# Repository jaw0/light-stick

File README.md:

LED based, battery powered light for photography + videography
modeled after Wescott's "Ice Light"

* aprox 4300 lumens

* 38 Watts

* adjustable power level

* adjustable color temperature: 2700K - 6500K

* consistent + stable output + color even as batteries die

* flicker free

* remembers settings when turned off

* OLED display + touch panel user interface

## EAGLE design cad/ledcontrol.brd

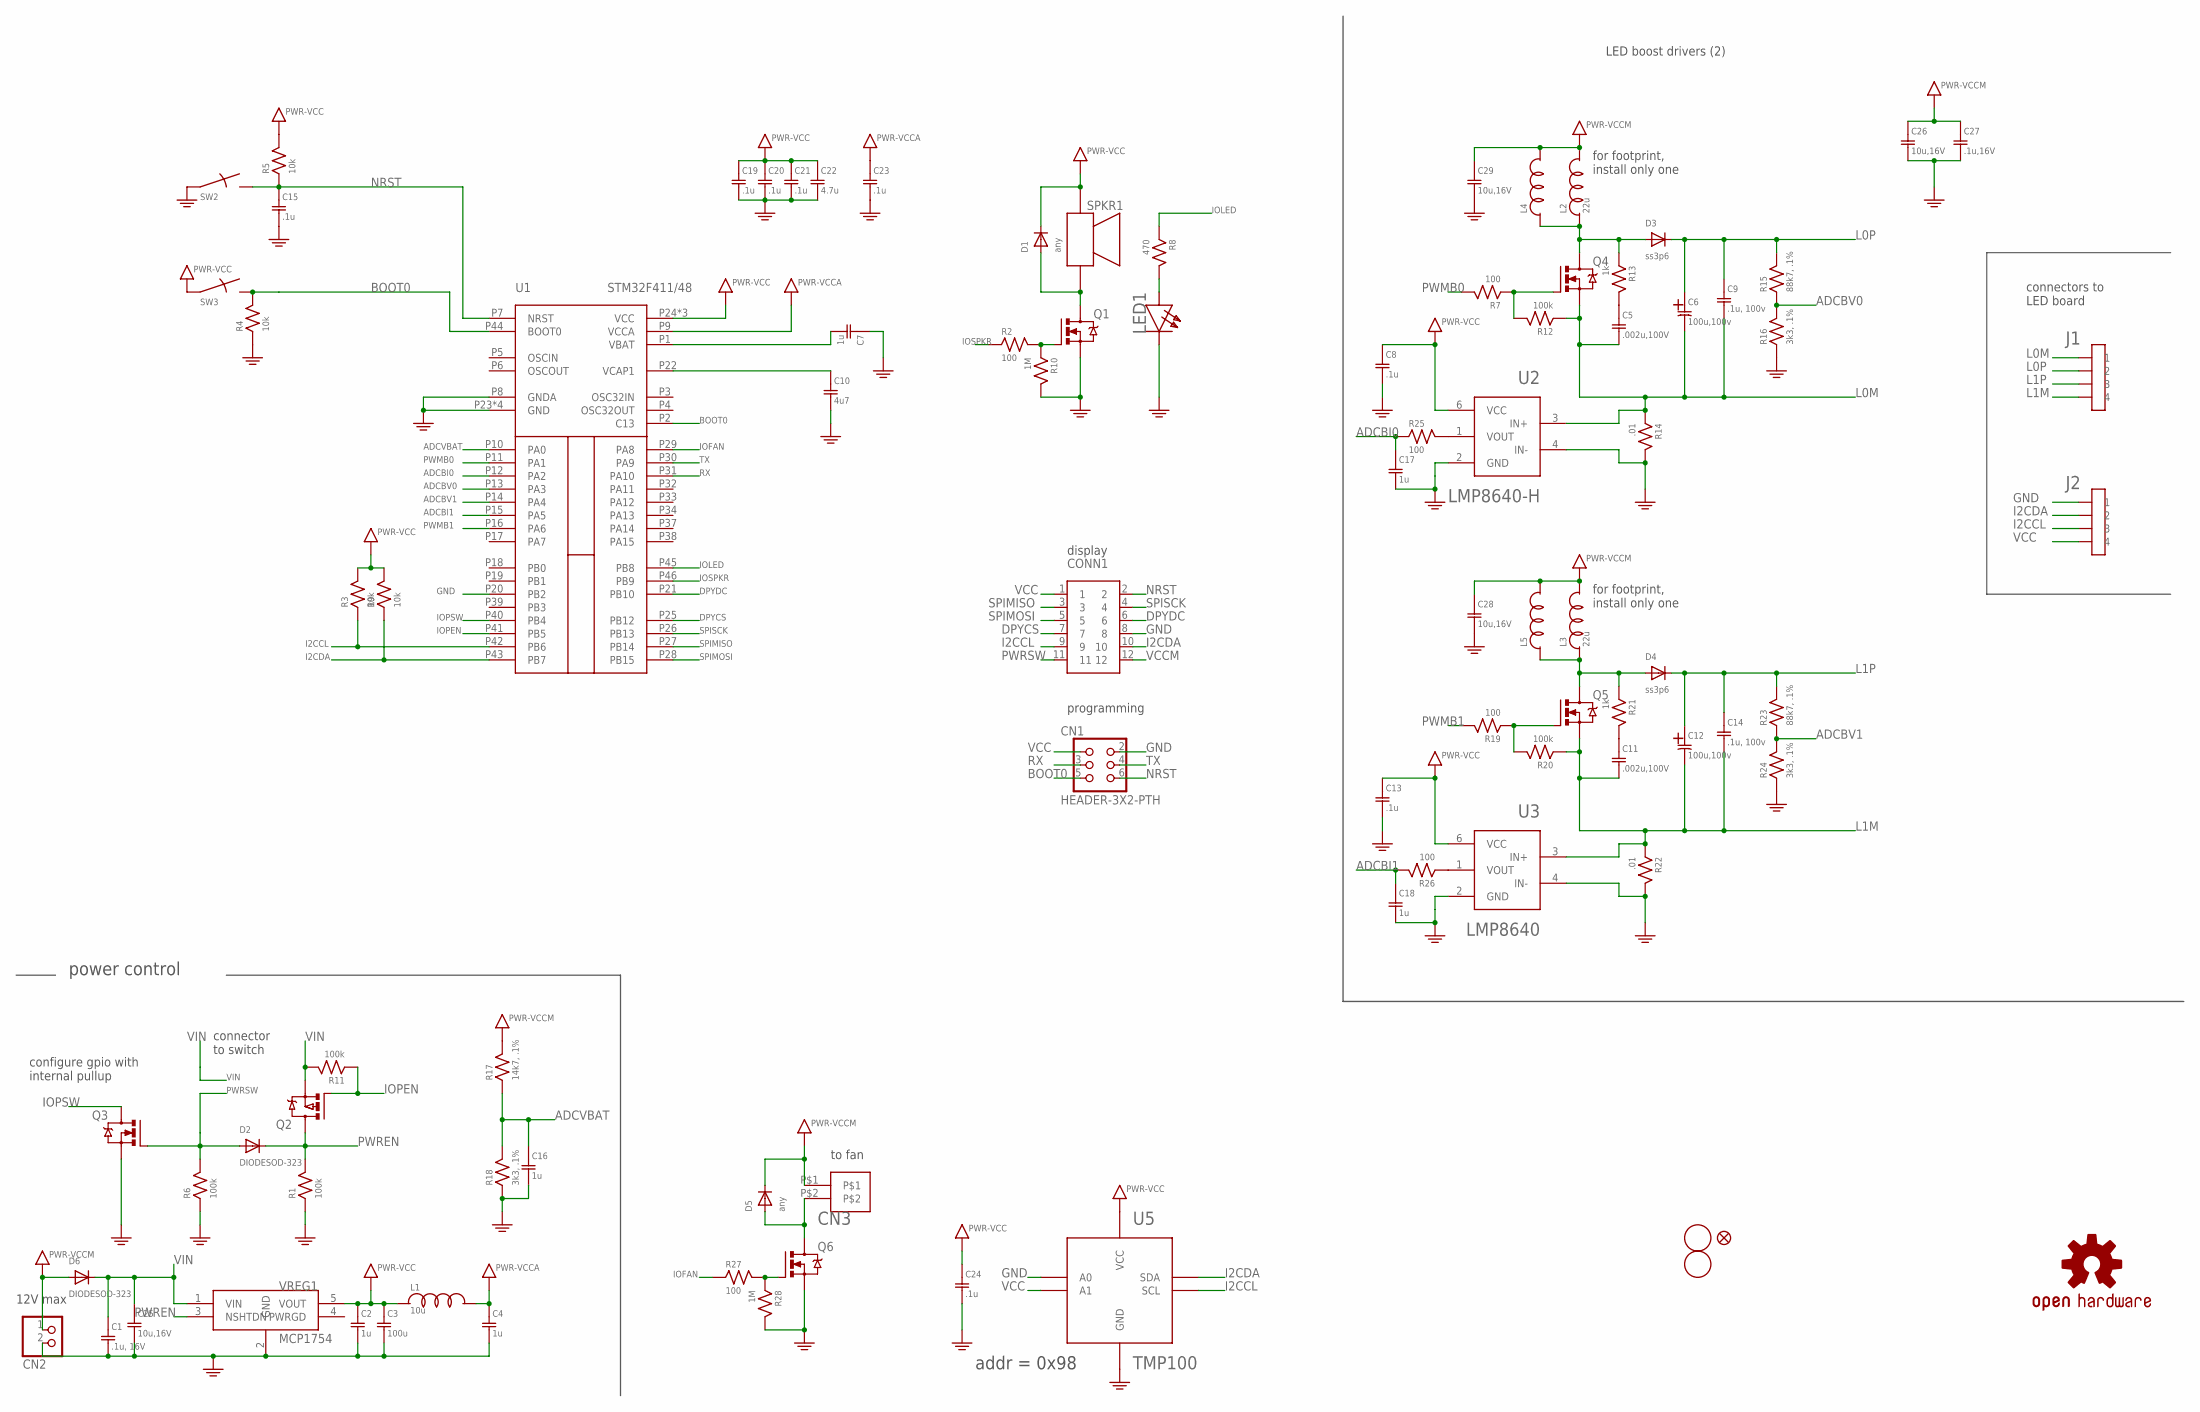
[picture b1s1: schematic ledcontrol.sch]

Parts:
C1: .1u, 16V; SMD0603
C2, C4, C7, C16, C17, C18: 1u; SMD0603
C3: 100u; SMD1210
C5, C11: .002u,100V; SMD0603
C6, C12: 100u,100v; CAPKE0
C8, C13, C15, C19, C20, C21, C23, C24: .1u; SMD0603
C9, C14: .1u, 100v; SMD0805
C10: 4u7; SMD0603
C22: 4.7u; SMD0603
C25, C26, C28, C29: 10u,16V; SMD0603
C27: .1u,16V; SMD0603
CN1: HEADER-3X2-PTH
CN2: JST_2PIN-THM-RA; JST-PH-2-THM-RA
CN3: HEADER-1X2-THM
CONN1: HEADER-6X2-PTH
D1, D5: any; SOD-323
D2, D6: DIODESOD-323; SOD-323
D3, D4: ss3p6; DO-214AC
FID1: FIDUCIALUFIDUCIAL; MICRO-FIDUCIAL
J1, J2: HEADER-4X1-PTH
L1: 10u; SMD0603
L2, L3: 22u; BOURNS2303
L4, L5: L-SRR1260; SRR1260
LED1: white; SMD0603D
LOGO1: OSHW-LOGOS; OSHW-LOGO-S
Q1, Q6: IRLML6344TRPBF; SOT-23-3
Q2: MOSFET-P; SOT-23-3@1
Q3: MOSFETSOT-23; SOT-23-3
Q4, Q5: AON6246; DFN5X6-8LEP1
R1, R6, R11, R12, R20: 100k; SMD0603
R2, R7, R19, R25, R26, R27: 100; SMD0603
R3, R4, R5, R9: 10k; SMD0603
R8: 470; SMD0603
R10, R28: 1M; SMD0603
R13, R21: 1k; SMD0603
R14, R22: .01; SMD1206
R15, R23: 88k7, .1%; SMD0603
R16, R18, R24: 3k3, .1%; SMD0603
R17: 14k7, .1%; SMD0603
SPKR1: PUI-5040; PUI-0540
SW2, SW3: SWITCHKMR211; KMR211
U1: STM32F411/48; UQPFN48
U2: LMP8640-H; SOT-23-6
U3: LMP8640; SOT-23-6
U5: TMP100; SOT-23-6
U$1, U$2: FIDUCIAL; FIDUCIAL_1MM
VREG1: MCP1754; SOT-23-5

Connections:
ADCBI0: C17.1, R25.1, U1.P12 (PA2)
ADCBI1: C18.1, R26.2, U1.P15 (PA5)
ADCBV0: R15.1, R16.2, U1.P13 (PA3)
ADCBV1: R23.1, R24.2, U1.P14 (PA4)
ADCVBAT: C16.1, R17.1, R18.2, U1.P10 (PA0)
BOOT0: CN1.5, R4.2, SW3.2, SW3.4, U1.P2 (C13), U1.P44 (BOOT0)
DPYCS: CONN1.7, U1.P25 (PB12)
DPYDC: CONN1.6, U1.P21 (PB10)
GND: C1.2, C2.2, C3.2, C4.2, C7.1, C8.2, C10.2, C13.2, C15.2, C16.2, C17.2, C18.2, C19.2, C20.2, C21.2, C22.2, C23.2, C24.2, C25.2, C26.2, C27.2, C28.2, C29.2, CN1.2, CN2.2 (1), CONN1.8, J2.P$1 (1), LED1.C, Q1.2 (S), Q3.2 (S), Q6.2 (S), R1.1, R4.1, R6.1, R10.2, R14.2, R16.1, R18.1, R22.2, R24.1, R28.2, SW2.1, SW2.3, U1.P8 (GNDA), U1.P20 (PB2), U1.P23 (GND), U1.P35 (GND), U1.P47 (GND), U1.PAD (GND), U2.2 (GND), U2.4 (IN-), U3.2 (GND), U3.4 (IN-), U5.2 (GND), U5.5 (A0), VREG1.2 (GND)
I2CCL: CONN1.9, J2.P$3 (3), R3.1, U1.P42 (PB6), U5.1 (SCL)
I2CDA: CONN1.10, J2.P$2 (2), R9.1, U1.P43 (PB7), U5.6 (SDA)
IOFAN: R27.1, U1.P29 (PA8)
IOLED: R8.1, U1.P45 (PB8)
IOPEN: Q2.1 (G), R11.1, U1.P41 (PB5)
IOPSW: Q3.3 (D), U1.P40 (PB4)
IOSPKR: R2.1, U1.P46 (PB9)
L0M: C5.2, C6.N, C9.2, J1.P$1 (1), Q4.P$1 (S), Q4.P$2 (S), Q4.P$3 (S), R12.1, R14.1, U2.3 (IN+)
L0P: C6.P, C9.1, D3.C, J1.P$2 (2), R15.2
L1M: C11.2, C12.N, C14.2, J1.P$4 (4), Q5.P$1 (S), Q5.P$2 (S), Q5.P$3 (S), R20.1, R22.1, U3.3 (IN+)
L1P: C12.P, C14.1, D4.C, J1.P$3 (3), R23.2
unnamed: D3.A, L2.P$1, L4.P$1, Q4.P$5 (D), Q4.P$6 (D), Q4.P$7 (D), Q4.P$8 (D), Q4.P$9 (D), R13.1
unnamed: C5.1, R13.2
unnamed: Q4.P$4 (G), R7.1, R12.2
unnamed: Q1.1 (G), R2.2, R10.1
unnamed: LED1.A, R8.2
unnamed: D4.A, L3.P$1, L5.P$1, Q5.P$5 (D), Q5.P$6 (D), Q5.P$7 (D), Q5.P$8 (D), Q5.P$9 (D), R21.1
unnamed: C11.1, R21.2
unnamed: D1.A, Q1.3 (D), SPKR1.P2
unnamed: Q5.P$4 (G), R19.1, R20.2
unnamed: R25.2, U2.1 (VOUT)
unnamed: R26.1, U3.1 (VOUT)
unnamed: C10.1, U1.P22 (VCAP1)
unnamed: CN3.P$2, D5.A, Q6.3 (D)
unnamed: Q6.1 (G), R27.2, R28.1
unnamed: C7.2, U1.P1 (VBAT)
NRST: C15.1, CN1.6, CONN1.2, R5.1, SW2.2, SW2.4, U1.P7 (NRST)
PWMB0: R7.2, U1.P11 (PA1)
PWMB1: R19.2, U1.P16 (PA6)
PWREN: D2.C, Q2.3 (D), R1.2, VREG1.3 (NSHTDN)
PWRSW: CONN1.11, D2.A, Q3.1 (G), R6.2
RX: CN1.3, U1.P31 (PA10)
SPIMISO: CONN1.3, U1.P27 (PB14)
SPIMOSI: CONN1.5, U1.P28 (PB15)
SPISCK: CONN1.4, U1.P26 (PB13)
TX: CN1.4, U1.P30 (PA9)
VCC: C2.1, C3.1, C8.1, C13.1, C19.1, C20.1, C21.1, C22.1, C24.1, CN1.1, CONN1.1, D1.C, J2.P$4 (4), L1.1, R3.2, R5.2, R9.2, SPKR1.P1, SW3.1, SW3.3, U1.P24 (VCC), U1.P36 (VCC), U1.P48 (VCC), U2.6 (VCC), U3.6 (VCC), U5.3 (A1), U5.4 (VCC), VREG1.5 (VOUT)
VCCA: C4.1, C23.1, L1.2, U1.P9 (VCCA)
VCCM: C26.1, C27.1, C28.1, C29.1, CN2.1 (2), CN3.P$1, CONN1.12, D5.C, D6.A, L2.P$2, L3.P$2, L4.P$2, L5.P$2, R17.2
VIN: C1.1, C25.1, D6.C, Q2.2 (S), R11.2, VREG1.1 (VIN)

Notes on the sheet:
configure gpio with internal pullup
power control
LED boost drivers (2)
connector to switch
12V max
display
programming
connectors to LED board
to fan
addr = 0x98
for footprint, install only one

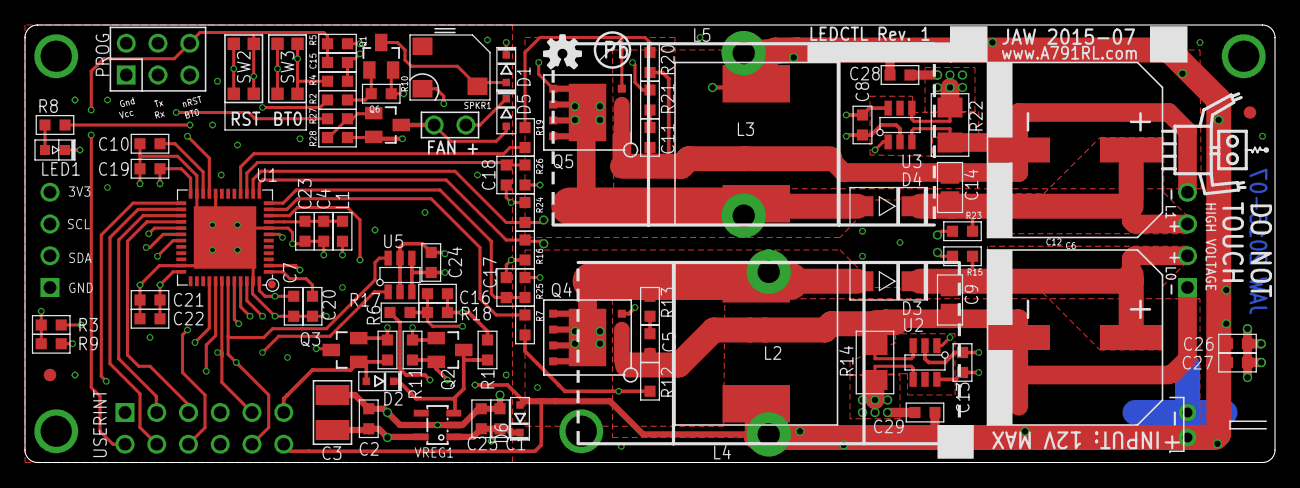
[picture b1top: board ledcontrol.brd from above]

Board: 4 copper layers, 100.0 x 35.0 mm, 93 parts (1 on the bottom side), 49 nets.

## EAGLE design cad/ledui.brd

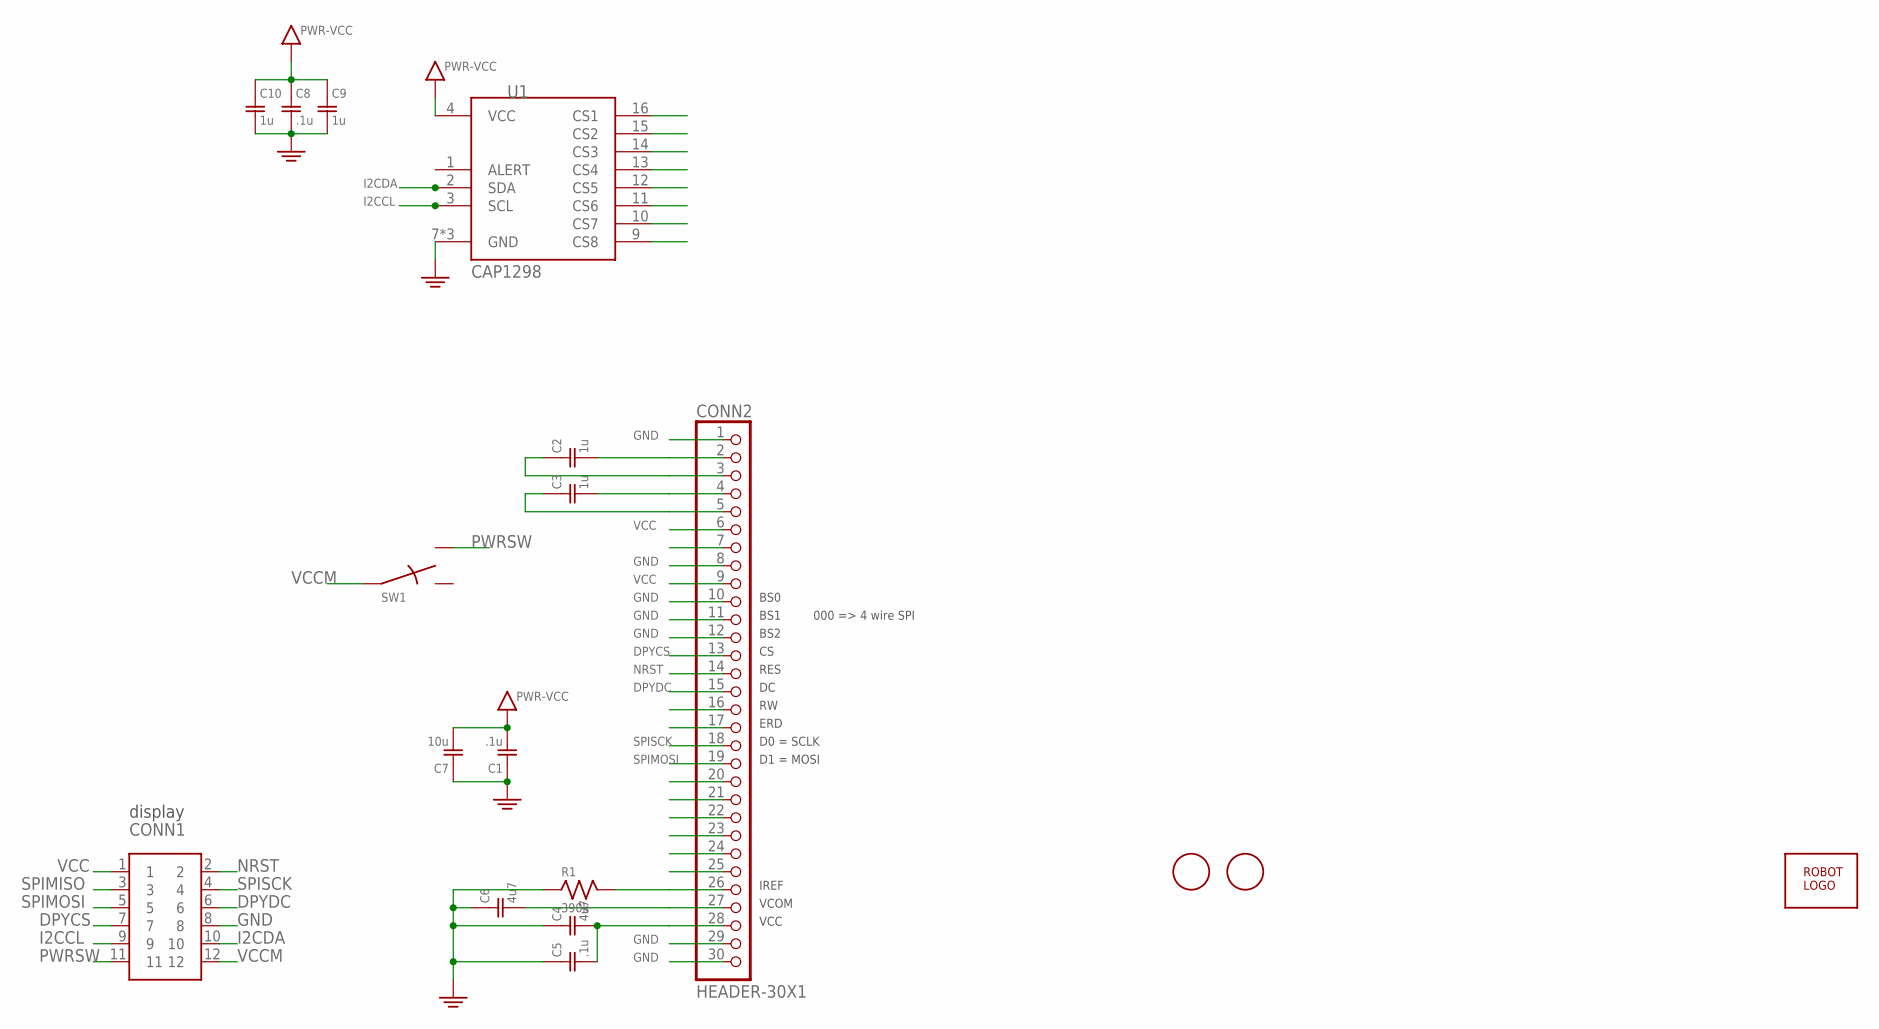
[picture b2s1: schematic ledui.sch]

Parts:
C1, C5, C8: .1u; SMD0603
C2, C3, C9, C10: 1u; SMD0603
C4, C6: 4u7; SMD0603
C7: 10u; SMD0603
CONN1: HEADER-6X2-PTH
CONN2: HEADER-30X1; HEADER-30X1-SMD7
R1: 390k; SMD0603
SW1: SWITCH-SPDT; ALPS-SSAJ120100
U1: CAP1298; QFN16EP
U$1, U$2: FIDUCIAL; FIDUCIAL_1MM
U$3: ROBOTMAN-LOGO

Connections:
CS1: U1.16 (CS1)
CS2: U1.15 (CS2)
CS3: U1.14 (CS3)
CS4: U1.13 (CS4)
CS5: U1.12 (CS5)
CS6: U1.11 (CS6)
CS7: U1.10 (CS7)
CS8: U1.9 (CS8)
DPYCS: CONN1.7, CONN2.13
DPYDC: CONN1.6, CONN2.15
GND: C1.1, C4.1, C5.1, C6.1, C7.1, C8.2, C9.2, C10.2, CONN1.8, CONN2.1, CONN2.8, CONN2.10, CONN2.11, CONN2.12, CONN2.29, CONN2.30, R1.1, U1.7 (GND), U1.8 (GND), U1.P$1 (GND)
I2CCL: CONN1.9, U1.3 (SCL)
I2CDA: CONN1.10, U1.2 (SDA)
unnamed: C3.2, CONN2.4
unnamed: C2.1, CONN2.3
unnamed: C3.1, CONN2.5
unnamed: C2.2, CONN2.2
unnamed: CONN2.26, R1.2
unnamed: C6.2, CONN2.27
unnamed: C4.2, C5.2, CONN2.28
NRST: CONN1.2, CONN2.14
PWRSW: CONN1.11, SW1.2
SPIMISO: CONN1.3
SPIMOSI: CONN1.5, CONN2.19
SPISCK: CONN1.4, CONN2.18
VCC: C1.2, C7.2, C8.1, C9.1, C10.1, CONN1.1, CONN2.6, CONN2.9, U1.4 (VCC)
VCCM: CONN1.12, SW1.C

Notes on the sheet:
display
BS0
BS1
BS2
000 => 4 wire SPI
RES
ERD
D0 = SCLK
D1 = MOSI
IREF
VCOM
VCC

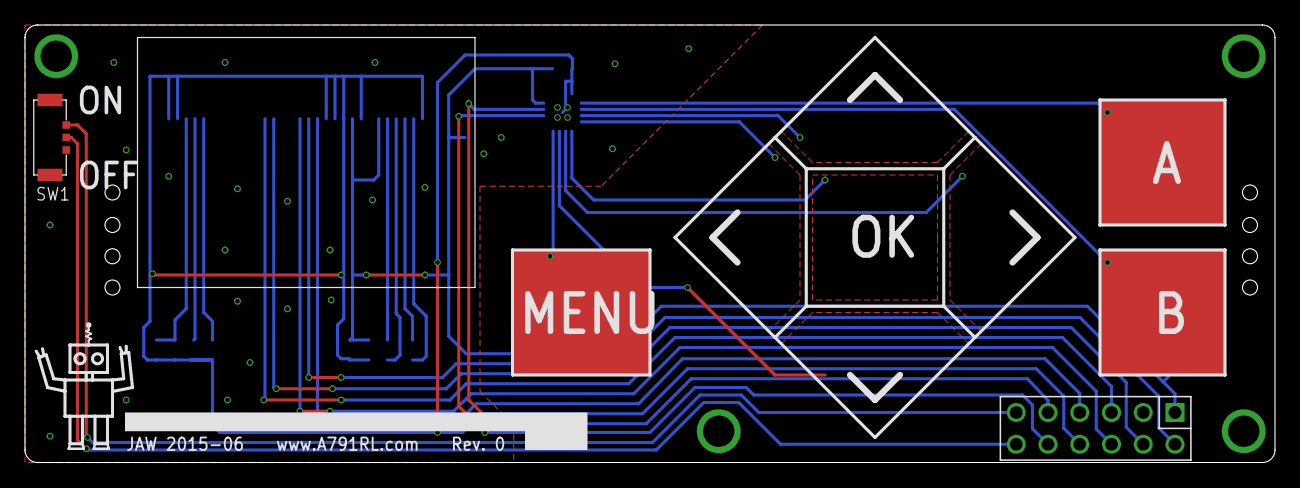
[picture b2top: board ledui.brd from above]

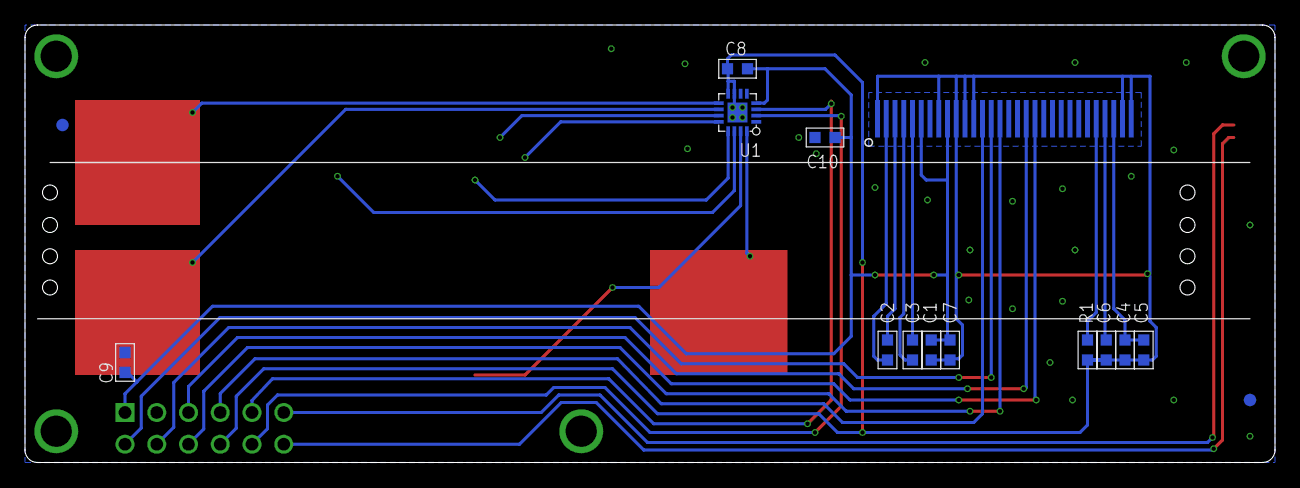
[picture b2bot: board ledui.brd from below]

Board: 2 copper layers, 100.0 x 35.0 mm, 18 parts (15 on the bottom side), 18 nets.

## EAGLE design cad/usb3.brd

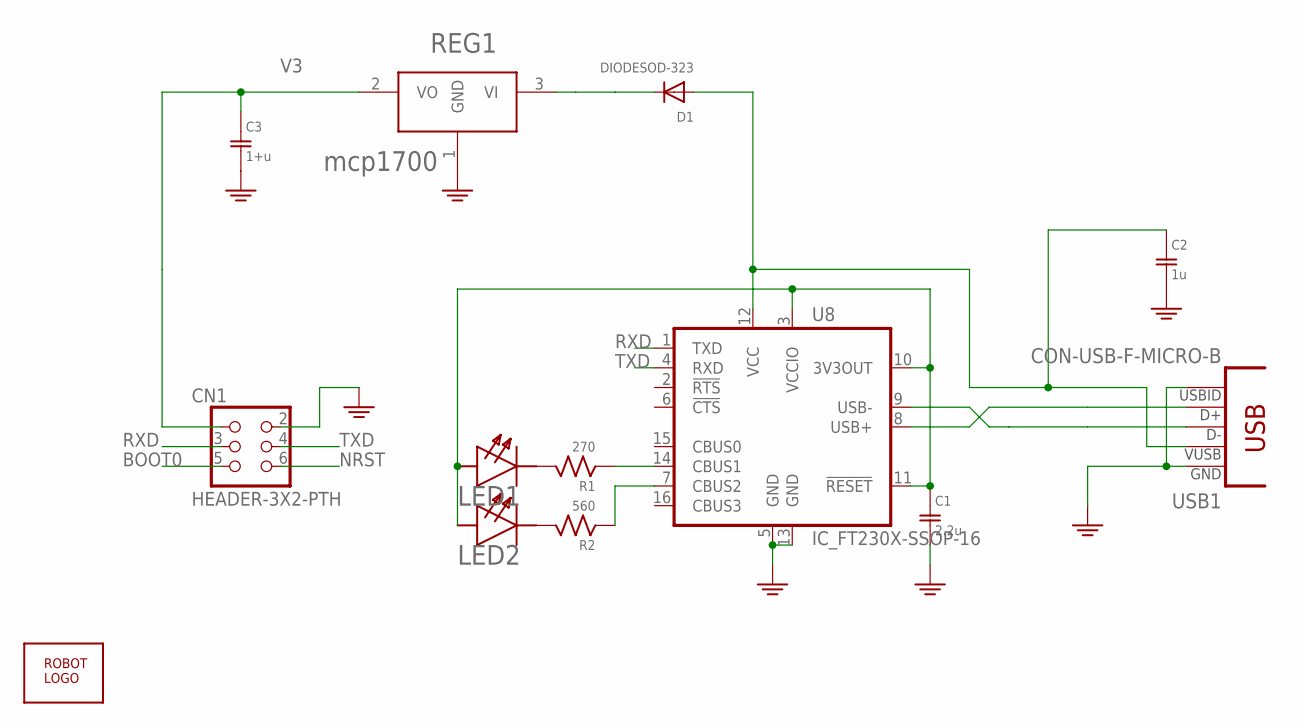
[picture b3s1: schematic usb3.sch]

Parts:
C1: 2.2u; SMD0603
C2: 1u; SMD0603
C3: 1+u; SMD0603
CN1: HEADER-3X2-PTH
D1: DIODESOD-323; SOD-323
LED1: GREEN; SMD0603D
LED2: ORANGE; SMD0603D
R1: 270; SMD0603
R2: 560; SMD0603
REG1: mcp1700; SOT-23-3
U8: IC_FT230X-SSOP-16; SSOP-16-FTDI
U$1: ROBOTMAN-LOGO
USB1: CON-USB-F-MICRO-B; CONN_USB_MICRO-B

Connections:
BOOT0: CN1.5
GND: C1.2, C2.2, C3.2, CN1.2, REG1.1 (GND), U8.5 (GND), U8.13 (GND), USB1.P4 (USBID), USB1.P5 (GND)
unnamed: D1.C, REG1.3 (VI)
unnamed: U8.8 (USB+), USB1.P3 (D+)
unnamed: U8.9 (USB-), USB1.P2 (D-)
unnamed: LED1.C, R1.2
unnamed: LED2.C, R2.2
unnamed: R1.1, U8.14 (CBUS1)
unnamed: R2.1, U8.7 (CBUS2)
NRST: CN1.6
RXD: CN1.3, U8.1 (TXD)
TXD: CN1.4, U8.4 (RXD)
USB3V3: C1.1, LED1.A, LED2.A, U8.3 (VCCIO), U8.10 (3V3OUT), U8.11 (!RESET)
V3: C3.1, CN1.1, REG1.2 (VO)
VBUS: C2.1, D1.A, U8.12 (VCC), USB1.P1 (VUSB)

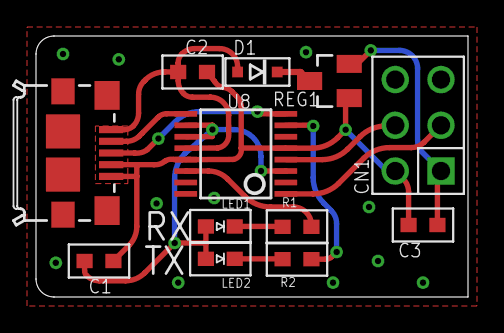
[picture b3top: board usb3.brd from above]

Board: 2 copper layers, 24.0 x 14.5 mm, 13 parts (1 on the bottom side), 13 nets.

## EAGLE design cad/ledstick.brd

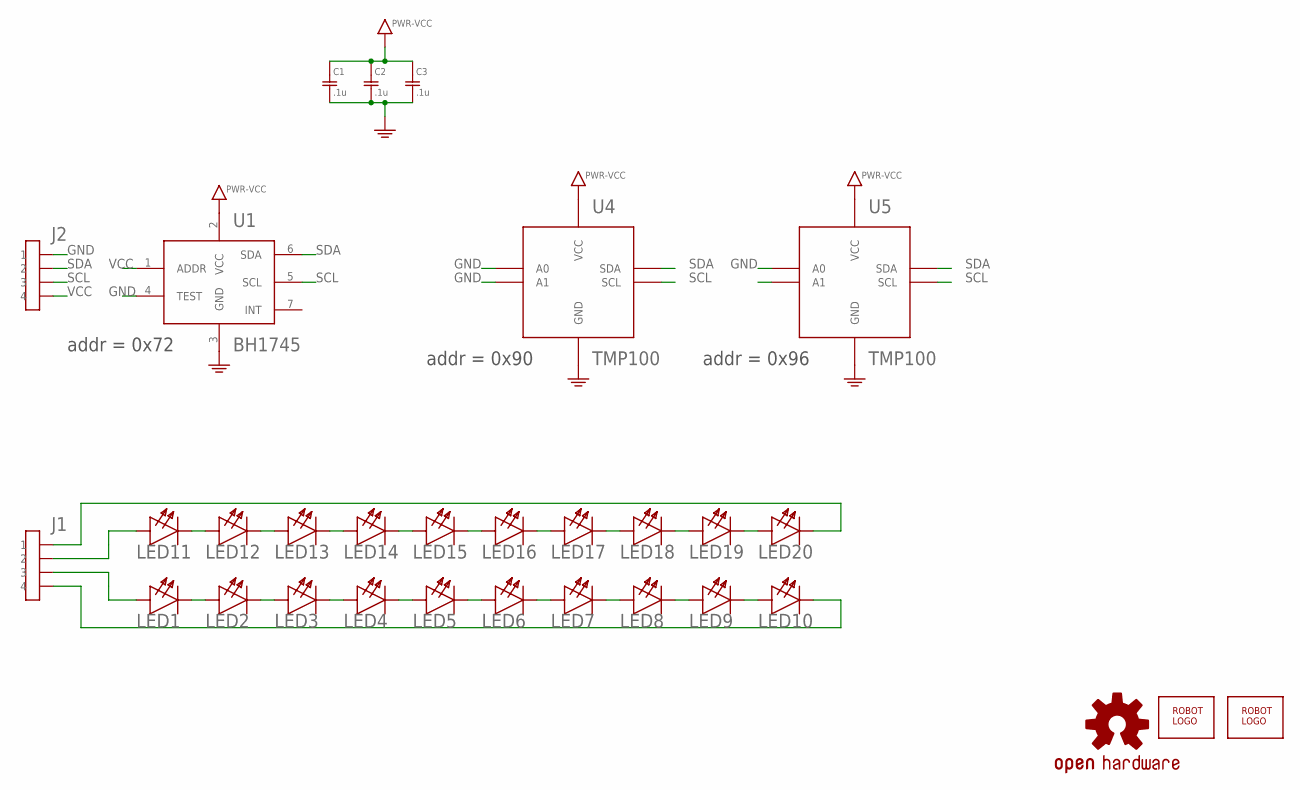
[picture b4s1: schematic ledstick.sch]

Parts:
C1, C2, C3: .1u; SMD0603
J1, J2: HEADER-4X1-PTH
LED1, LED2, LED3, LED4, LED5, LED6, LED7, LED8, LED9, LED10: W; LED4-4P1A
LED11, LED12, LED13, LED14, LED15, LED16, LED17, LED18, LED19, LED20: C; LED4-4P1A
LOGO1: OSHW-LOGOM; OSHW-LOGO-M
U1: BH1745; WSON8
U4, U5: TMP100; SOT-23-6
U$1, U$2: ROBOTMAN-LOGO

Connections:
GND: C1.2, C2.2, C3.2, J2.P$1 (1), U1.3 (GND), U1.4 (TEST), U4.2 (GND), U4.3 (A1), U4.5 (A0), U5.2 (GND), U5.5 (A0)
unnamed: LED1.C, LED2.A, LED2.AP (A)
unnamed: LED2.C, LED3.A, LED3.AP (A)
unnamed: LED3.C, LED4.A, LED4.AP (A)
unnamed: LED4.C, LED5.A, LED5.AP (A)
unnamed: LED5.C, LED6.A, LED6.AP (A)
unnamed: LED6.C, LED7.A, LED7.AP (A)
unnamed: LED7.C, LED8.A, LED8.AP (A)
unnamed: LED8.C, LED9.A, LED9.AP (A)
unnamed: LED9.C, LED10.A, LED10.AP (A)
unnamed: LED11.C, LED12.A, LED12.AP (A)
unnamed: LED12.C, LED13.A, LED13.AP (A)
unnamed: LED13.C, LED14.A, LED14.AP (A)
unnamed: LED14.C, LED15.A, LED15.AP (A)
unnamed: LED15.C, LED16.A, LED16.AP (A)
unnamed: LED16.C, LED17.A, LED17.AP (A)
unnamed: LED17.C, LED18.A, LED18.AP (A)
unnamed: LED18.C, LED19.A, LED19.AP (A)
unnamed: LED19.C, LED20.A, LED20.AP (A)
unnamed: J1.P$2 (2), LED11.A, LED11.AP (A)
unnamed: J1.P$3 (3), LED1.A, LED1.AP (A)
unnamed: J1.P$1 (1), LED20.C
unnamed: J1.P$4 (4), LED10.C
SCL: J2.P$3 (3), U1.5 (SCL), U4.1 (SCL), U5.1 (SCL)
SDA: J2.P$2 (2), U1.6 (SDA), U4.6 (SDA), U5.6 (SDA)
VCC: C1.1, C2.1, C3.1, J2.P$4 (4), U1.1 (ADDR), U1.2 (VCC), U4.4 (VCC), U5.4 (VCC)

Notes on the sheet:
addr = 0x90
addr = 0x96
addr = 0x72

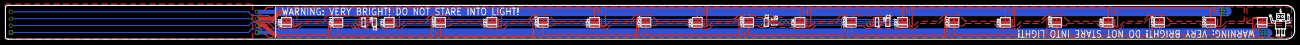
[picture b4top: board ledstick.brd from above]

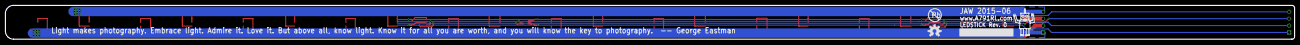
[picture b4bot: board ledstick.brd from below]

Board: 2 copper layers, 477.0 x 12.5 mm, 31 parts (2 on the bottom side), 26 nets.

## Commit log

2015-06-10 initial
2015-06-14 tweak
2015-07-17 more power
2015-08-10 fan, clean
2015-08-10 gitignore
2015-08-10 add images
2015-08-10 I am allergic to bananas

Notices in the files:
parts and their libraries:
SparkFun-Aesthetics: Licensing: Creative Commons ShareAlike 4.0 International - https://creativecommons.org/licenses/by-sa/4.0
